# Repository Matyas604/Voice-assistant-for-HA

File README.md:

# Voice assistant for HA
A while back, I saw a YouTube video about a voice assistant for [Home Assistant](https://www.home-assistant.io/). I really liked that it activates when you say “Hey Jarvis” and can control various things via voice commands. 
And since I have Home Assistant set up, I thought, why not try building that assistant myself?

I found out that voice recognition can run on the [ESP32-S3-WROOM-1-N16R8](https://m5stack-doc.oss-cn-shenzhen.aliyuncs.com/1183/ESP32-S3-WROOM-1U-N16R8.pdf), so I decided to use it because it’s relatively inexpensive. 
Since I also wanted it to have a high-quality speaker for playing music, the total cost is quite high, but that’s because of the speaker, the custom PCB, and other components. 

I really enjoyed working on this project because I learned a lot of new things. For example, I learned how to properly design a speaker enclosure, since sound quality depends more on the enclosure than on the speaker itself.

## Features
- Power and programming are handled via the **USB-C** port on the back
- The [ESP32-S3](https://m5stack-doc.oss-cn-shenzhen.aliyuncs.com/1183/ESP32-S3-WROOM-1U-N16R8.pdf) is the brain of the entire voice assistant
- It uses **Groq AI**, **GroqTTS**, and **Groq STT**, so it can speak and understand many languages
- It's not just a voice assistant for commands, but also a great AI assistant
- It has internet access, so it can search for information and use it to provide answers
- Everything is accompanied by a light response, so you know exactly what's going on
- It's also a great music player because it features a high-quality [DAYTON DMA45-4](https://www.reproobchod.cz/user/related_files/dma45-4.pdf) speaker
- It has a touch button to mute the assistant hidden in the top cover.

⚠️As you can see, the project is fully functional, but it’s missing the case because I had a few issues with the printer in printing legion and it didn’t arrive in time for the deadline. That’s why I’m submitting it to the build review like this for now, but as soon as the case arrives, I’ll document it again. Thank you

I really enjoyed designing and then building this project, especially because it works absolutely great. There was one error in the PCB (it’s already been corrected in the schematic and files), but fortunately it wasn’t a huge one and was easy to fix. This was actually my first project to include SMD components, and I soldered it by hand. The hardest part was soldering the amplifier chip, but luckily I managed to do it in the end!

Now, here's how it works: Once it's set up correctly, all you have to do is say "Hey Jarvis" and give your command or ask your question, and it will respond immediately or perform the action you requested. [Here](https://github.com/Matyas604/Voice-assistant-for-HA/blob/main/How%20to%20Set%20It%20Up.md) are the complete instructions on how to set it up.

## CAD model
Everything is housed in a box consisting of 5 parts (front panel, rear panel, top panel, body, and a tube connecting the outside to the inside chamber). The touch button is hidden in the top panel, so it can be activated by touch and is not visible from the outside. The interior space behind the speaker must be completely airtight at the front to function properly; it is connected to the outside only by a tube at the back. It is also a good idea to place a piece of cotton wool inside for better sound quality. The PCB is located separately from the space around the speaker; it is secured with M3 screws, just like the rear panel, while the top panel is held in place by magnets. 

<p align="center">
  <strong>Made in Fusion360</strong>
</p>

## PCB
<p align="center">
  Schematic
</p>

<p align="center">
  PCB
</p>

<p align="center">
  <strong>Made in KiCad</strong>
</p>

## Firmware
This voice assistant uses [ESPHome](https://esphome.io/) firmware. It is programmed via the USB-C port. It is activated by saying "Hey Jarvis" and sends a recording of the command to the [Home Assistant](https://www.home-assistant.io/), where it is converted to text using **Groq STT**, then converted into a response using **Groq AI**, and then converted into a voice response using **Groq TTS**, the action is performed, and the response is spoken. You need to have the voice assistant pipeline set up correctly in Home Assistant tutorial [here](https://github.com/Matyas604/Voice-assistant-for-HA/blob/main/How%20to%20Set%20It%20Up.md)!

## BOM
You can find it in .csv format [here](https://github.com/Matyas604/Voice-assistant-for-HA/blob/main/BOM.csv). 

<hr>

<p align="center">
  Made with ❤️ by <a href="https://github.com/Matyas604">@Matyas604</a>
</p>

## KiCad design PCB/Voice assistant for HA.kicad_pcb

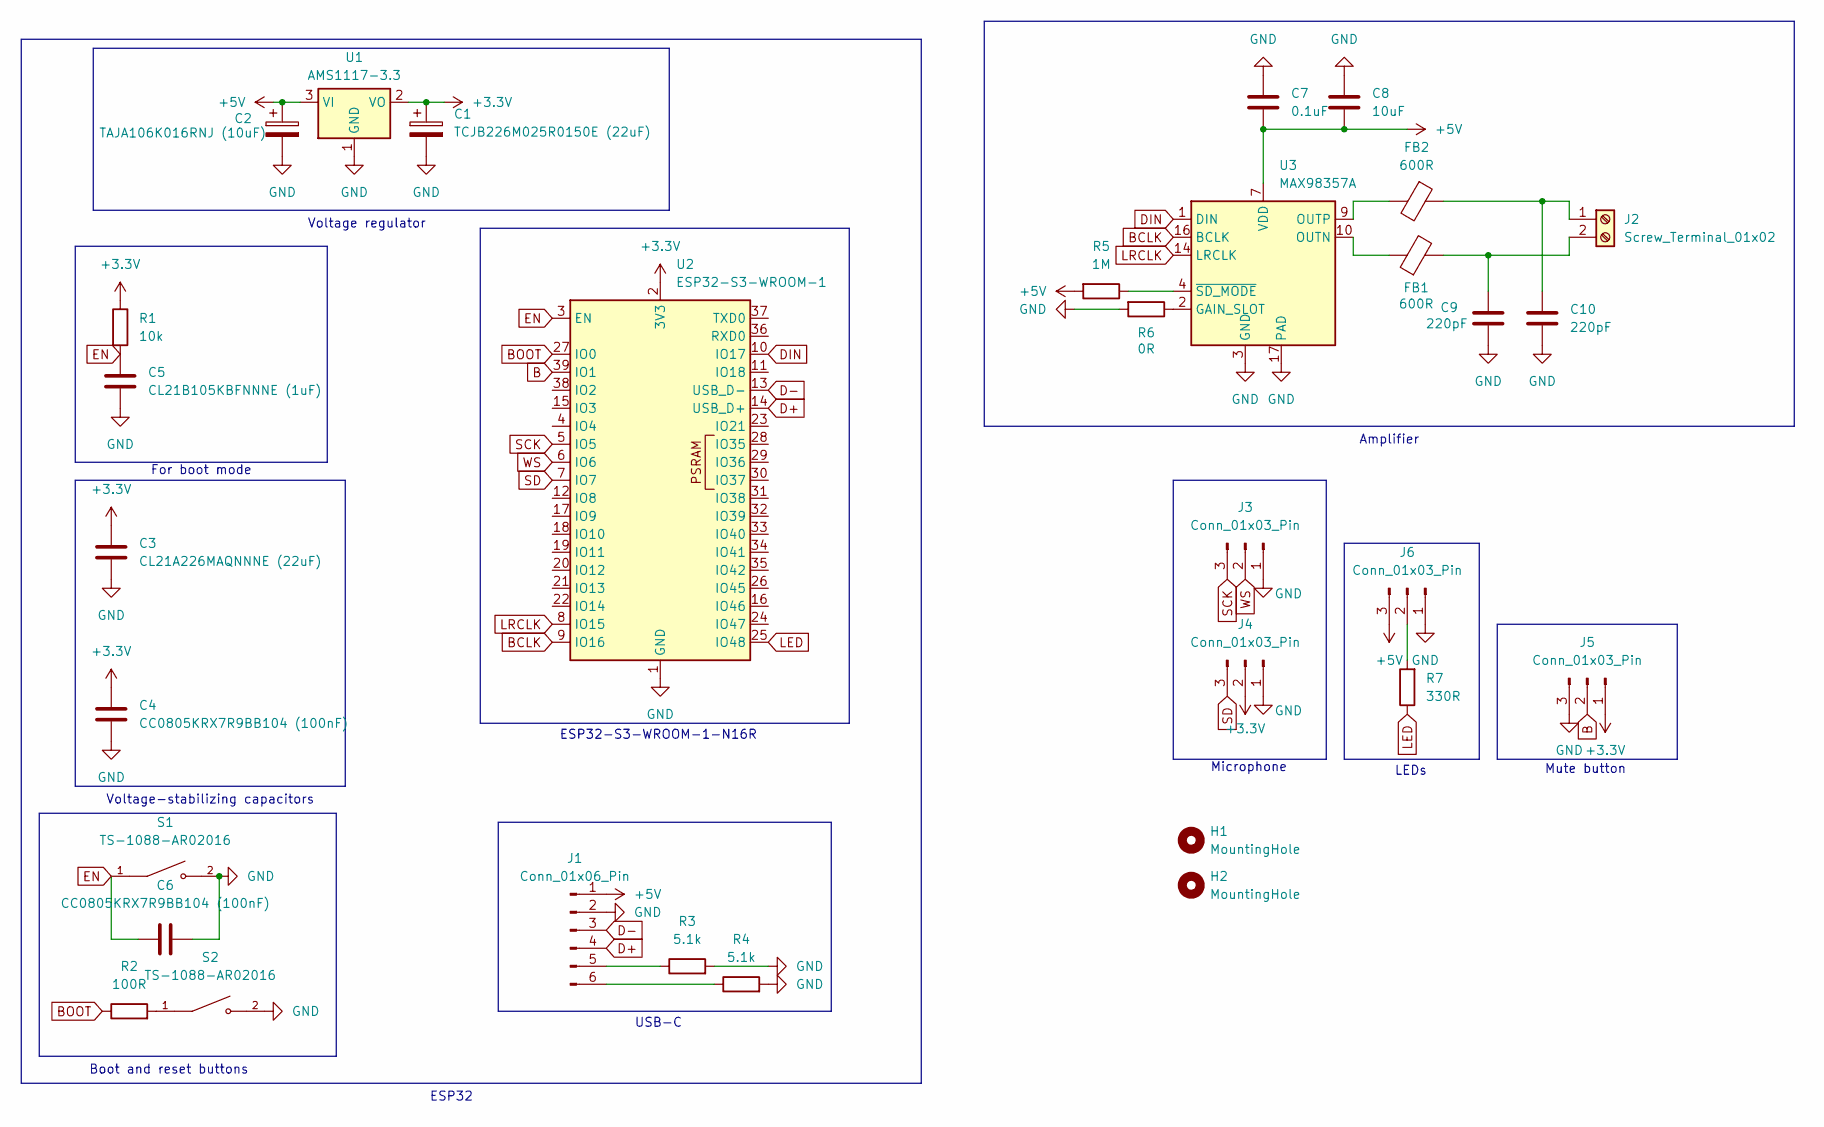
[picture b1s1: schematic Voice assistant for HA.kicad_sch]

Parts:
C1: TCJB226M025R0150E (22uF); CP_EIA-3528-21_Kemet-B
C2: TAJA106K016RNJ (10uF); CP_EIA-3216-18_Kemet-A
C3: CL21A226MAQNNNE (22uF); C_0805_2012Metric
C4, C6: CC0805KRX7R9BB104 (100nF); C_0805_2012Metric
C5: CL21B105KBFNNNE (1uF); C_0805_2012Metric
C7: 0.1uF; C_0805_2012Metric
C8: 10uF; C_0805_2012Metric
C9, C10: 220pF; C_0805_2012Metric
FB1, FB2: 600R; L_0805_2012Metric
H1, H2: MountingHole; MountingHole_3.2mm_M3
J1: Conn_01x06_Pin; PinHeader_1x06_P2.54mm_Vertical
J2: Screw_Terminal_01x02; TerminalBlock_Phoenix_MKDS-1,5-2_1x02_P5.00mm_Horizontal
J3, J4, J5, J6: Conn_01x03_Pin; PinHeader_1x03_P2.54mm_Vertical
R1: 10k; R_0805_2012Metric
R2: 100R; R_0805_2012Metric
R3, R4: 5.1k; R_0805_2012Metric
R5: 1M; R_0805_2012Metric
R6: 0R; R_0805_2012Metric
R7: 330R; R_0805_2012Metric
S1, S2: TS-1088-AR02016; SW_TS-1088-AR02016; PARTREV N/A
U1: AMS1117-3.3; SOT-223-3_TabPin2
U2: ESP32-S3-WROOM-1
U3: MAX98357A; TQFN-16-1EP_3x3mm_P0.5mm_EP1.23x1.23mm_ThermalVias

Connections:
+3.3V: C1.1, C3.1, C4.1, J4.2, J5.1, R1.1, U1.2 (VO), U2.2 (3V3)
+5V: C2.1, C7.2, C8.2, J1.1, J6.3, R5.2, U1.3 (VI), U3.7 (VDD), U3.8 (VDD)
B: J5.2, U2.39 (IO1)
BCLK: U2.9 (IO16), U3.16 (BCLK)
BOOT: R2.1, U2.27 (IO0)
D+: J1.4, U2.14 (USB_D+)
D-: J1.3, U2.13 (USB_D-)
DIN: U2.10 (IO17), U3.1 (DIN)
EN: C5.2, C6.1, R1.2, S1.1, U2.3 (EN)
GND: C1.2, C2.2, C3.2, C4.2, C5.1, C6.2, C7.1, C8.1, C9.2, C10.2, J1.2, J3.1, J4.1, J5.3, J6.1, R3.2, R4.2, R6.2, S1.2, S2.2, U1.1 (GND), U2.1 (GND), U2.40 (GND), U2.41 (GND), U3.3 (GND), U3.11 (GND), U3.15 (GND), U3.17 (PAD)
LED: R7.1, U2.25 (IO48)
LRCLK: U2.8 (IO15), U3.14 (LRCLK)
unnamed: J1.5, R3.1
unnamed: J1.6, R4.1
unnamed: C10.1, FB2.1, J2.1
unnamed: C9.1, FB1.2, J2.2
unnamed: J6.2, R7.2
unnamed: R2.2, S2.1
unnamed: R6.1, U3.2 (GAIN_SLOT)
unnamed: FB1.1, U3.10 (OUTN)
unnamed: FB2.2, U3.9 (OUTP)
unnamed: R5.1, U3.4 (~SD_MODE)
SCK: J3.3, U2.5 (IO5)
SD: J4.3, U2.7 (IO7)
WS: J3.2, U2.6 (IO6)

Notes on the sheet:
Voltage-stabilizing capacitors
LEDs
For boot mode
USB-C
Amplifier
Microphone
Mute button
ESP32
Voltage regulator
ESP32-S3-WROOM-1-N16R
Boot and reset buttons

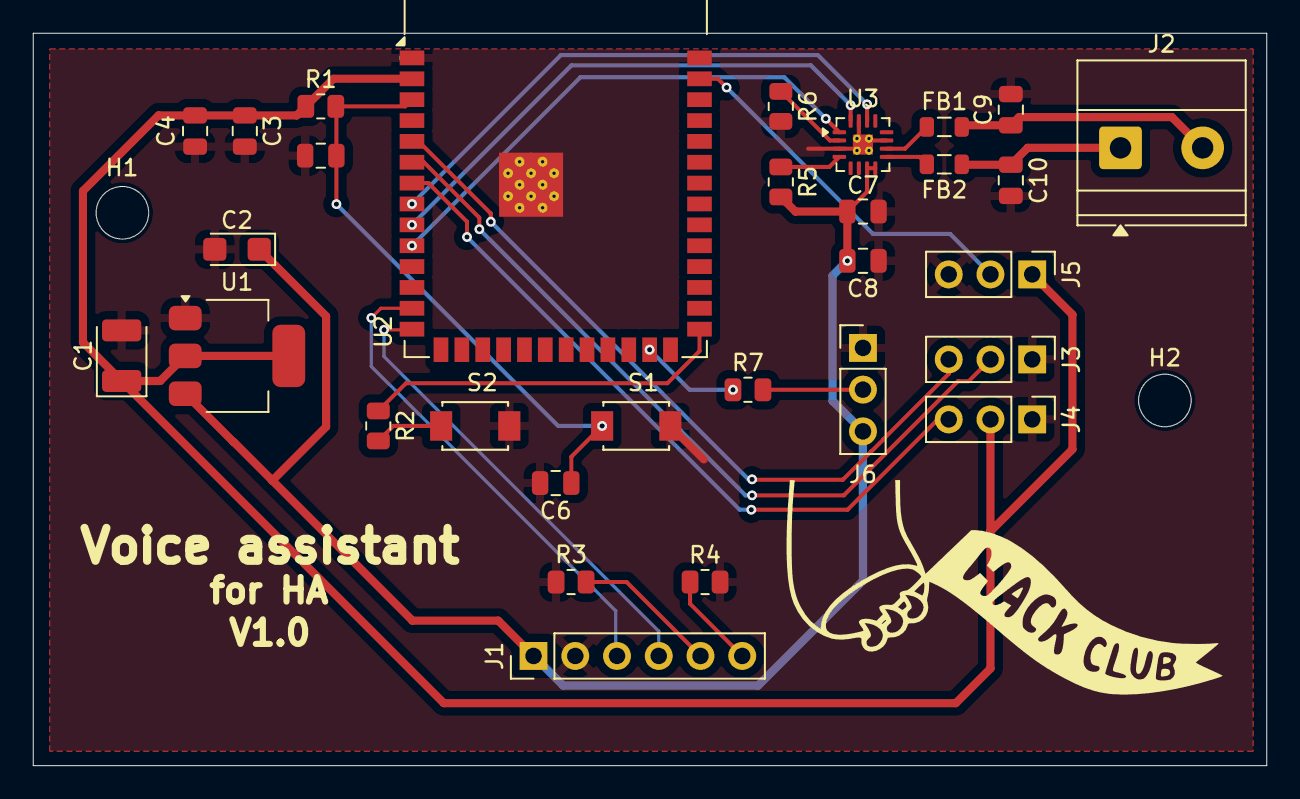
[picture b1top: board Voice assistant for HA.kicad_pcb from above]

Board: 2 copper layers, 75.1 x 44.6 mm, 32 parts (0 on the bottom side), 25 nets.

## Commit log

2026-04-13 Adding libraries
2026-04-13 Adding files
2026-04-13 Adding firmware
2026-04-13 Adding gerbers
2026-04-14 Adding BOM
2026-04-14 Done
2026-04-14 Final fix
2026-04-14 Adding CAD photo
2026-04-14 Adding PCb photos
2026-06-30 post-assembly adjustments
2026-06-30 Adding build photo
2026-06-30 Adding ESPHome screenshots
2026-06-30 Document setup process for Assistant integration
    Added detailed setup instructions for integrating the Assistant with Home Assistant and ESPHome, including steps for uploading code, configuring STT and TTS, and using Groq as an alternative to Gemin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
